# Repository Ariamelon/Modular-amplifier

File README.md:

# Modular amplifier
A PCB for a compact but complete headphone amplifier package. Designed to fit in [this](https://item.taobao.com/item.htm?id=629378026025) case.

## Key Features
* Swappable amplifier and relay attenuator modules
* Large heatsink with variable position based on thermal planes of amplifier modules
* +-13.7V voltage rails for the amplifier modules
* +5V secondary rail for the microcontroller, relays and logic
* Power on/off anti-thump functionality
* DC offset and overheat protection
* Differential/SE mode
* Mute mode
* Standby mode

An on-board ATtiny2313A-P is used to control these functions:
* 4-channel 256-step relay-based attenuator controlled via a standard pot
* RGB state indicator LED (because why not)

[PCB_Backplane](Images/Backplane-Assembly.pdf)

[PCB_Attenuator](Images/Attenuator-Assembly.pdf) 

[PCB_Omicron_Module](Images/Omicron_Module-Assembly.pdf)

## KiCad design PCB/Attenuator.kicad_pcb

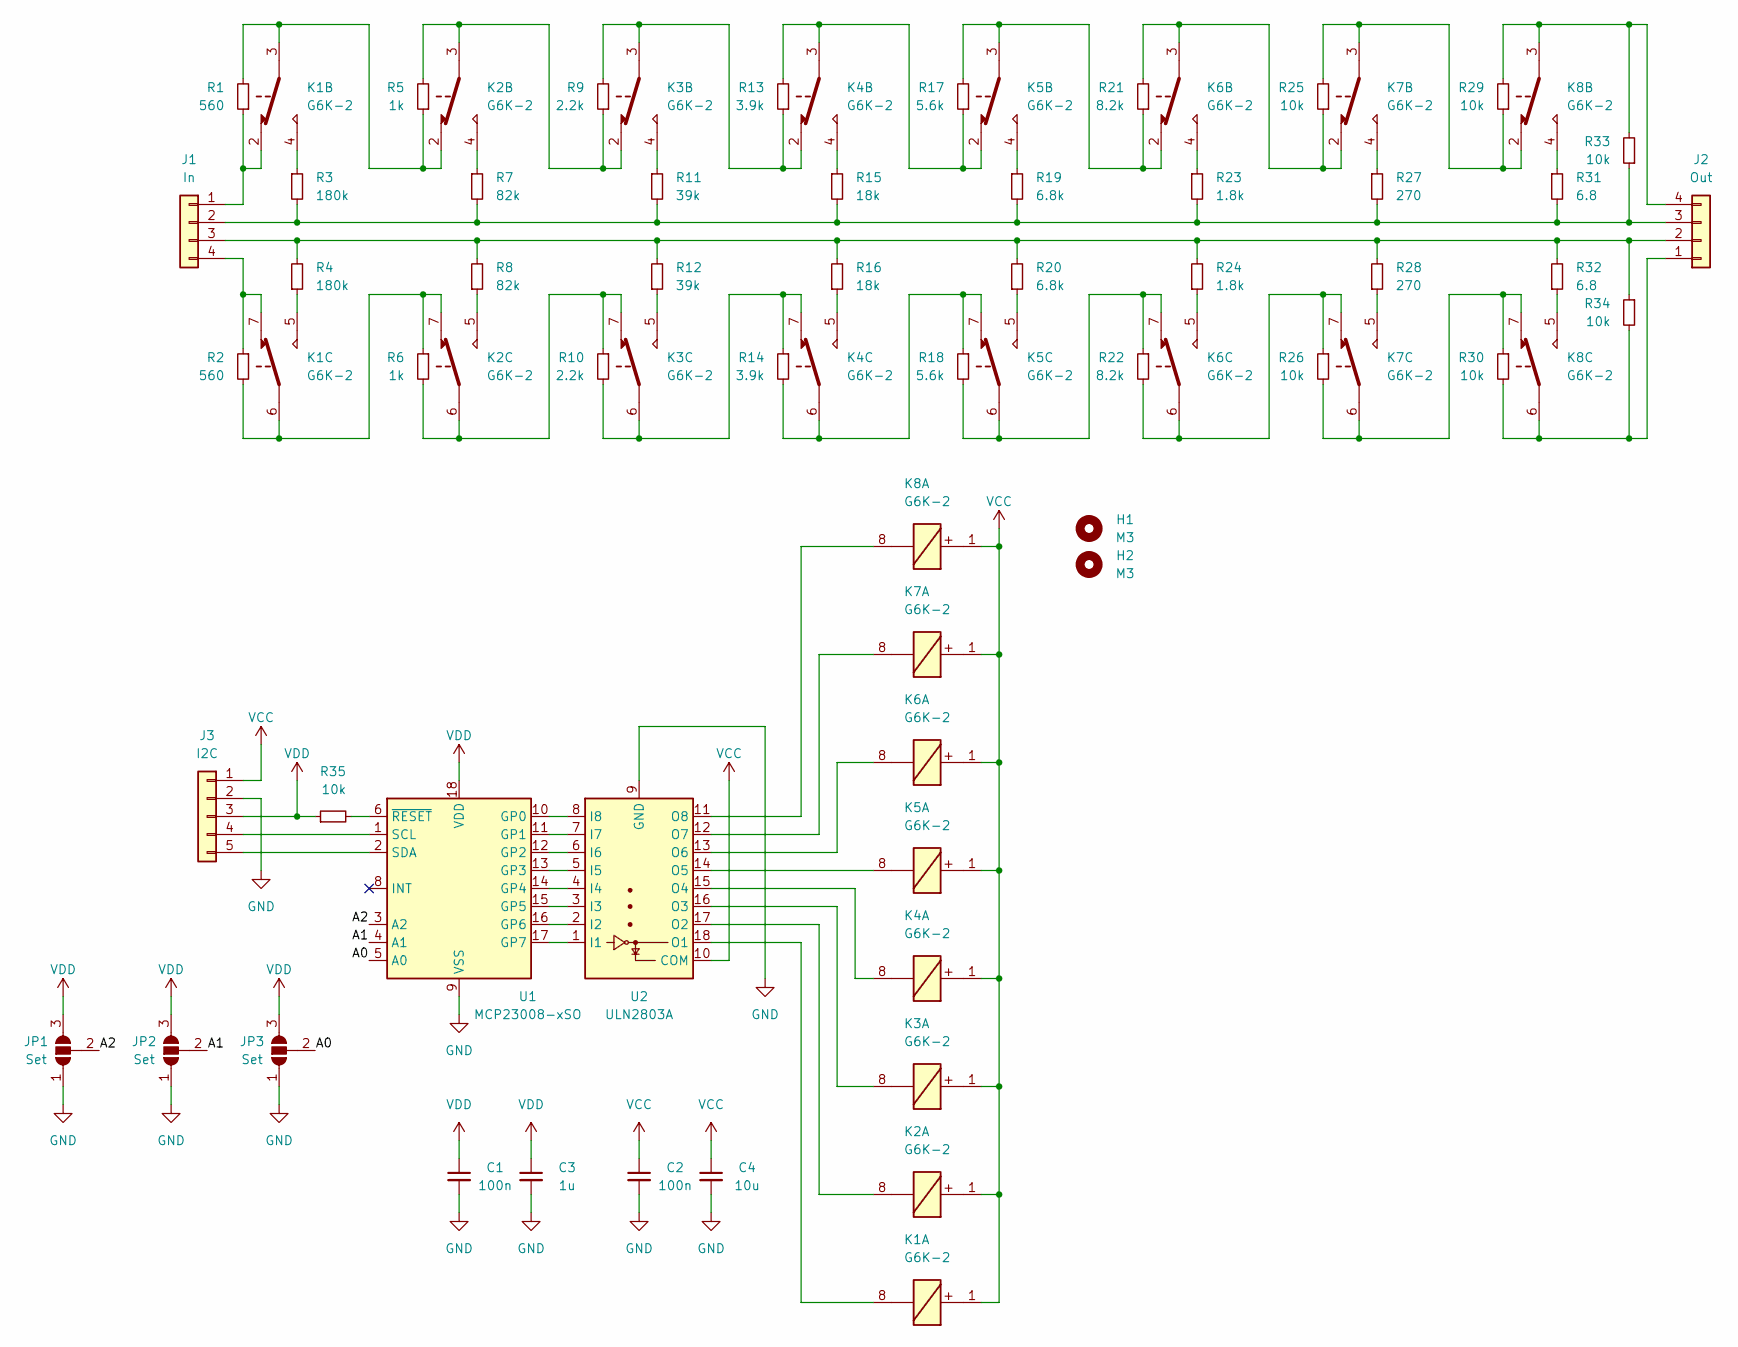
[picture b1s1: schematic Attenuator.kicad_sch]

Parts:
C1, C2: 100n; C_0603_1608Metric; Part number CL10A105KB8NNNC; LCSC part number C15849
C3: 1u; C_0603_1608Metric; Part number CL10A105KB8NNNC; LCSC part number C15849
C4: 10u; C_0603_1608Metric; Part number CL10A105KB8NNNC; LCSC part number C15849
H1, H2: M3; MountingHole_3.2mm_M3_DIN965_Pad
J1: In; PinSocket_1x04_P2.54mm_Horizontal
J2: Out; PinSocket_1x04_P2.54mm_Horizontal
J3: I2C; PinSocket_1x05_P2.54mm_Horizontal
JP1, JP2, JP3: Set; SolderJumper-3_P1.3mm_Open_RoundedPad1.0x1.5mm
K1, K2, K3, K4, K5, K6, K7, K8: G6K-2; Relay_DPDT_Omron_G6K-2P-Y
R1, R2: 560; R_1206_3216Metric
R3, R4: 180k; R_1206_3216Metric
R5, R6: 1k; R_1206_3216Metric
R7, R8: 82k; R_1206_3216Metric
R9, R10: 2.2k; R_1206_3216Metric
R11, R12: 39k; R_1206_3216Metric
R13, R14: 3.9k; R_1206_3216Metric
R15, R16: 18k; R_1206_3216Metric
R17, R18: 5.6k; R_1206_3216Metric
R19, R20: 6.8k; R_1206_3216Metric
R21, R22: 8.2k; R_1206_3216Metric
R23, R24: 1.8k; R_1206_3216Metric
R25, R26, R29, R30, R33, R34, R35: 10k; R_1206_3216Metric
R27, R28: 270; R_1206_3216Metric
R31, R32: 6.8; R_1206_3216Metric
U1: MCP23008-xSO; DIP-18_W7.62mm_Socket
U2: ULN2803A; DIP-18_W7.62mm_Socket

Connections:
/A0: JP3.2 (C), U1.5 (A0)
/A1: JP2.2 (C), U1.4 (A1)
/A2: JP1.2 (C), U1.3 (A2)
GND: C1.2, C2.2, C3.2, C4.2, J3.2, JP1.1 (A), JP2.1 (A), JP3.1 (A), U1.9 (VSS), U2.9 (GND)
unnamed: J1.1, K1.2, R1.1
unnamed: J1.2, J2.3, R3.2, R7.2, R11.2, R15.2, R19.2, R23.2, R27.2, R31.2, R33.1
unnamed: J1.3, J2.2, R4.2, R8.2, R12.2, R16.2, R20.2, R24.2, R28.2, R32.2, R34.1
unnamed: J1.4, K1.7, R2.1
unnamed: J2.1, K8.6, R30.2, R34.2
unnamed: J2.4, K8.3, R29.2, R33.2
unnamed: J3.4, U1.1 (SCL)
unnamed: J3.5, U1.2 (SDA)
unnamed: K1.3, K2.2, R1.2, R5.1
unnamed: K1.4, R3.1
unnamed: K1.5, R4.1
unnamed: K1.6, K2.7, R2.2, R6.1
unnamed: K1.8, U2.18 (O1)
unnamed: K2.3, K3.2, R5.2, R9.1
unnamed: K2.4, R7.1
unnamed: K2.5, R8.1
unnamed: K2.6, K3.7, R6.2, R10.1
unnamed: K2.8, U2.17 (O2)
unnamed: K3.3, K4.2, R9.2, R13.1
unnamed: K3.4, R11.1
unnamed: K3.5, R12.1
unnamed: K3.6, K4.7, R10.2, R14.1
unnamed: K3.8, U2.16 (O3)
unnamed: K4.3, K5.2, R13.2, R17.1
unnamed: K4.4, R15.1
unnamed: K4.5, R16.1
unnamed: K4.6, K5.7, R14.2, R18.1
unnamed: K4.8, U2.15 (O4)
unnamed: K5.3, K6.2, R17.2, R21.1
unnamed: K5.4, R19.1
unnamed: K5.5, R20.1
unnamed: K5.6, K6.7, R18.2, R22.1
unnamed: K5.8, U2.14 (O5)
unnamed: K6.3, K7.2, R21.2, R25.1
unnamed: K6.4, R23.1
unnamed: K6.5, R24.1
unnamed: K6.6, K7.7, R22.2, R26.1
unnamed: K6.8, U2.13 (O6)
unnamed: K7.3, K8.2, R25.2, R29.1
unnamed: K7.4, R27.1
unnamed: K7.5, R28.1
unnamed: K7.6, K8.7, R26.2, R30.1
unnamed: K7.8, U2.12 (O7)
unnamed: K8.4, R31.1
unnamed: K8.5, R32.1
unnamed: K8.8, U2.11 (O8)
unnamed: R35.2, U1.6 (~RESET)
unnamed: U1.10 (GP0), U2.8 (I8)
unnamed: U1.11 (GP1), U2.7 (I7)
unnamed: U1.12 (GP2), U2.6 (I6)
unnamed: U1.13 (GP3), U2.5 (I5)
unnamed: U1.14 (GP4), U2.4 (I4)
unnamed: U1.15 (GP5), U2.3 (I3)
unnamed: U1.16 (GP6), U2.2 (I2)
unnamed: U1.17 (GP7), U2.1 (I1)
VCC: C2.1, C4.1, J3.1, K1.1, K2.1, K3.1, K4.1, K5.1, K6.1, K7.1, K8.1, U2.10 (COM)
VDD: C1.1, C3.1, J3.3, JP1.3 (B), JP2.3 (B), JP3.3 (B), R35.1, U1.18 (VDD)

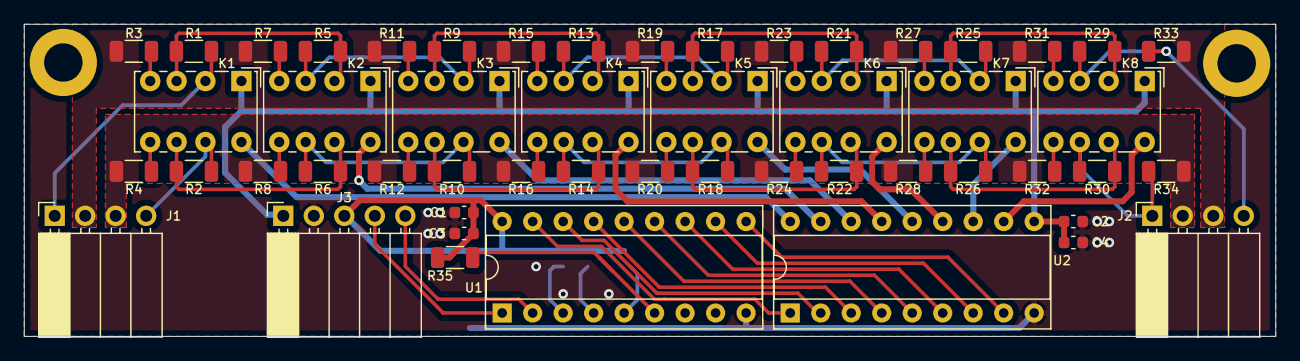
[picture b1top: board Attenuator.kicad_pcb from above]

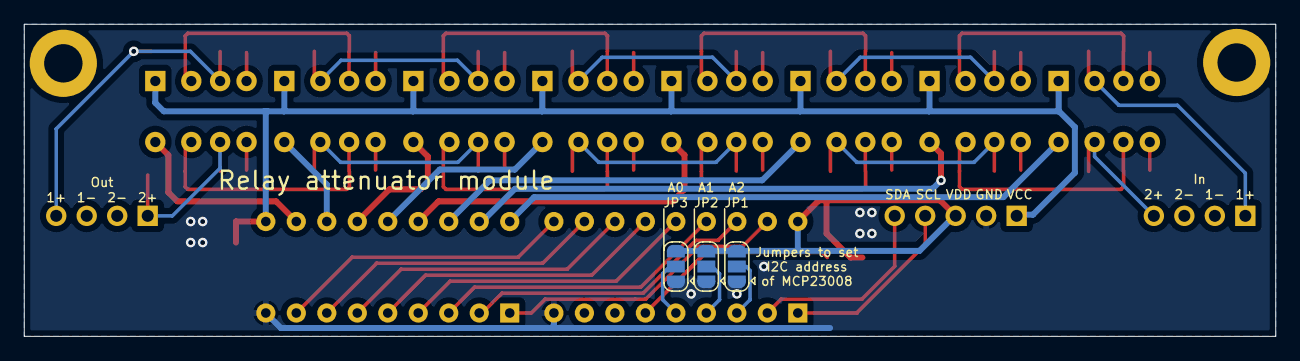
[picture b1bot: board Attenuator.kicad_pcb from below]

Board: 2 copper layers, 104.2 x 26.0 mm, 57 parts (3 on the bottom side), 61 nets.

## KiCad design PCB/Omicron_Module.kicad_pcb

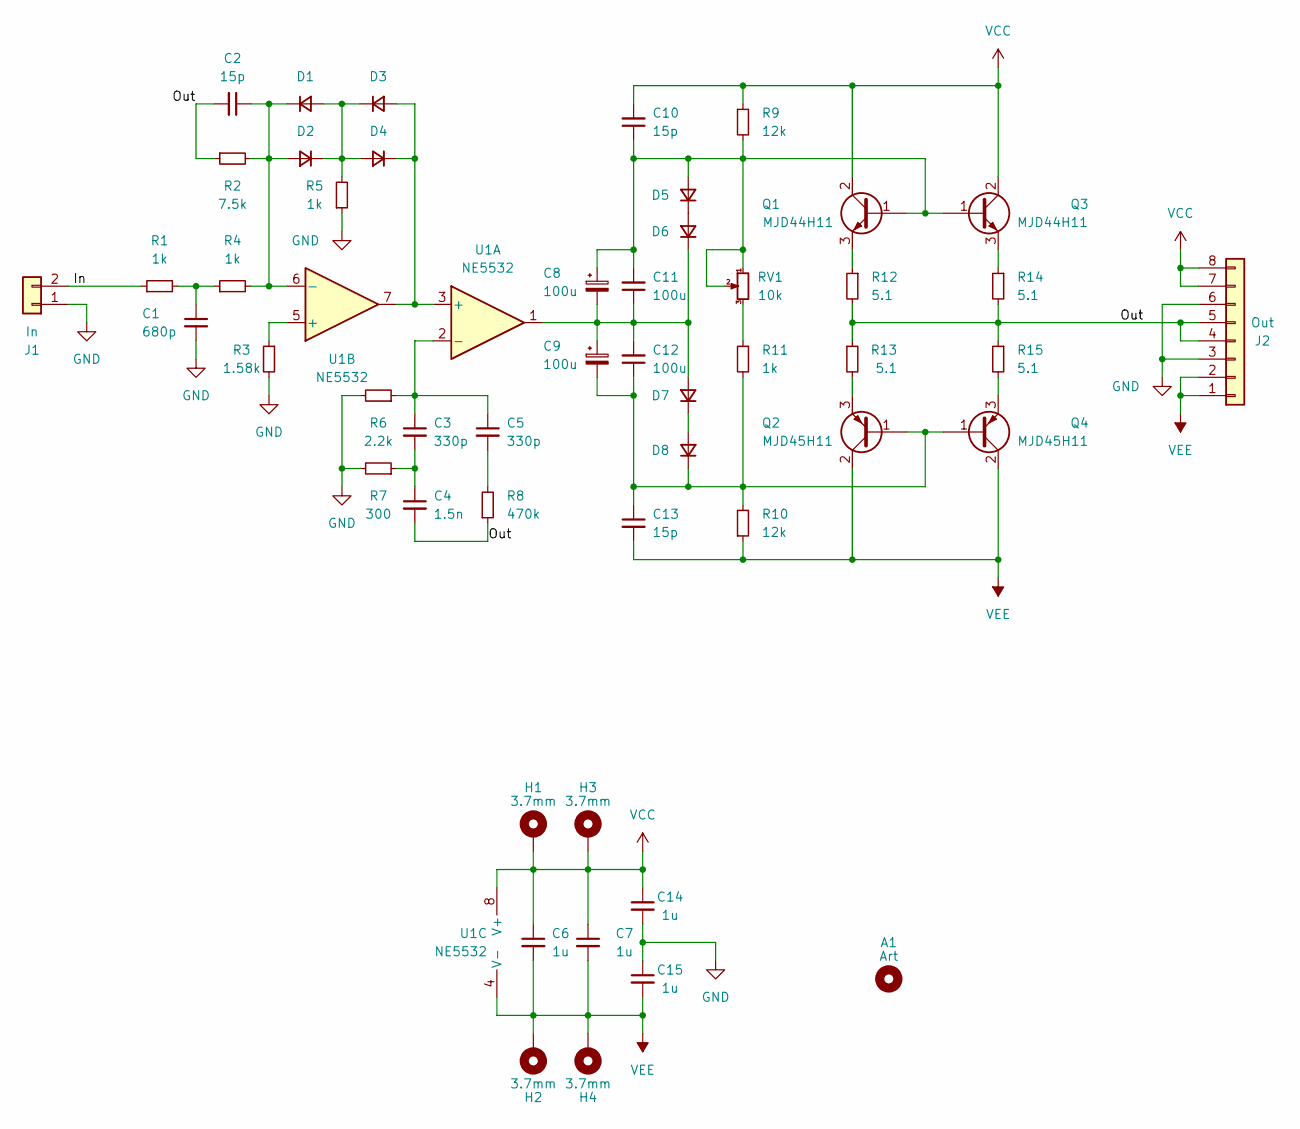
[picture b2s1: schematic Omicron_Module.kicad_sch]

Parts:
A1: Art; Ariamelon_Logo_CU
C1: 680p; C_0603_1608Metric
C2, C10, C13: 15p; C_0603_1608Metric
C3, C5: 330p; C_0603_1608Metric
C4: 1.5n; C_0603_1608Metric
C6, C7, C14, C15: 1u; C_0603_1608Metric; Part number CL10A105KB8NNNC; LCSC part number C15849
C8, C9: 100u; CP_Elec_8x6.9; Part number EEE-FK1V101GV
C11, C12: 100u; C_Radial_D8.0mm_H11.5mm_P3.50mm_Sideways; Part number EEE-FK1V101GV
D1, D2, D3, D4, D5, D6, D7, D8: D; D_SOD-123; Part number 1N4148W; LCSC part number C81598
H1, H2, H3, H4: 3.7mm; MountingHole_3.2mm_M3_DIN965_Pad_3.7mm_Hole
J1: In; PinHeader_1x02_P2.54mm_Vertical
J2: Out; PinHeader_1x08_P2.54mm_Vertical
Q1, Q3: MJD44H11; TO-252-2
Q2, Q4: MJD45H11; TO-252-2
R1, R4, R5, R11: 1k; R_1206_3216Metric
R2: 7.5k; R_1206_3216Metric
R3: 1.58k; R_1206_3216Metric
R6: 2.2k; R_1206_3216Metric
R7: 300; R_1206_3216Metric
R8: 470k; R_1206_3216Metric
R9, R10: 12k; R_1206_3216Metric
R12, R13, R14, R15: 5.1; R_1206_3216Metric
RV1: 10k; Potentiometer_Bourns_TC33X_Vertical
U1: NE5532; SOIC-8_3.9x4.9mm_P1.27mm

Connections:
/In: J1.2, R1.1
/Out: C2.2, C4.2, J2.4, J2.5, R2.1, R8.1, R12.2, R13.1, R14.2, R15.1
GND: C1.2, C14.2, C15.1, J1.1, J2.3, J2.6, R3.2, R5.1, R6.2, R7.2
unnamed: C1.1, R1.2, R4.1
unnamed: C2.1, D1.1 (K), D2.2 (A), R2.2, R4.2, U1.6 (-)
unnamed: C3.1, C5.1, R6.1, U1.2 (-)
unnamed: C3.2, C4.1, R7.1
unnamed: C5.2, R8.2
unnamed: C8.1, C10.1, C11.2, D5.2 (A), Q1.1 (B), Q3.1 (B), R9.2, RV1.1, RV1.2
unnamed: C8.2, C9.1, C11.1, C12.2, D6.1 (K), D7.2 (A), U1.1
unnamed: C9.2, C12.1, C13.1, D8.1 (K), Q2.1 (B), Q4.1 (B), R10.2, R11.2
unnamed: D1.2 (A), D2.1 (K), D3.1 (K), D4.2 (A), R5.2
unnamed: D3.2 (A), D4.1 (K), U1.3 (+), U1.7
unnamed: D5.1 (K), D6.2 (A)
unnamed: D7.1 (K), D8.2 (A)
unnamed: Q1.3 (E), R12.1
unnamed: Q2.3 (E), R13.2
unnamed: Q3.3 (E), R14.1
unnamed: Q4.3 (E), R15.2
unnamed: R3.1, U1.5 (+)
unnamed: R11.1, RV1.3
VCC: C6.1, C7.1, C10.2, C14.1, H1.1, H3.1, J2.7, J2.8, Q1.2 (C), Q3.2 (C), R9.1, U1.8 (V+)
VEE: C6.2, C7.2, C13.2, C15.2, H2.1, H4.1, J2.1, J2.2, Q2.2 (C), Q4.2 (C), R10.1, U1.4 (V-)

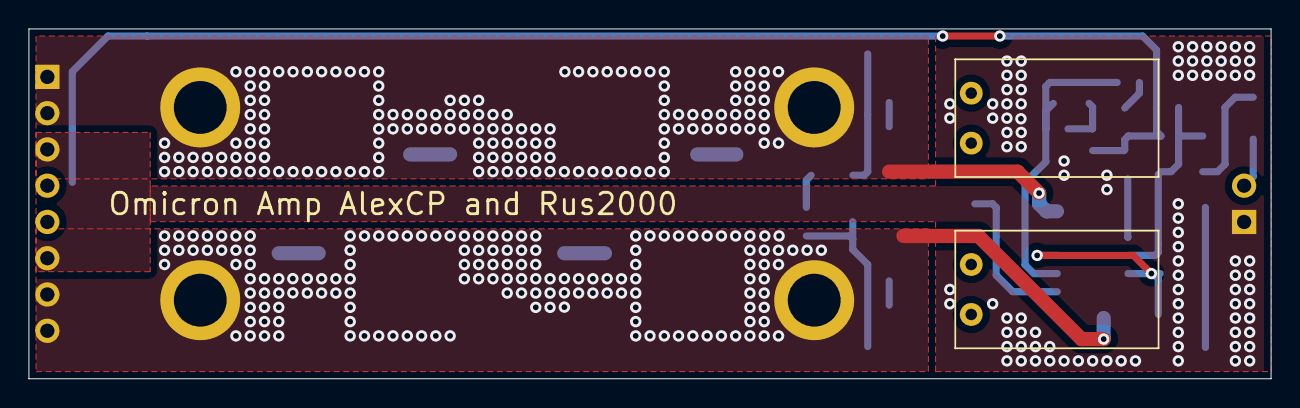
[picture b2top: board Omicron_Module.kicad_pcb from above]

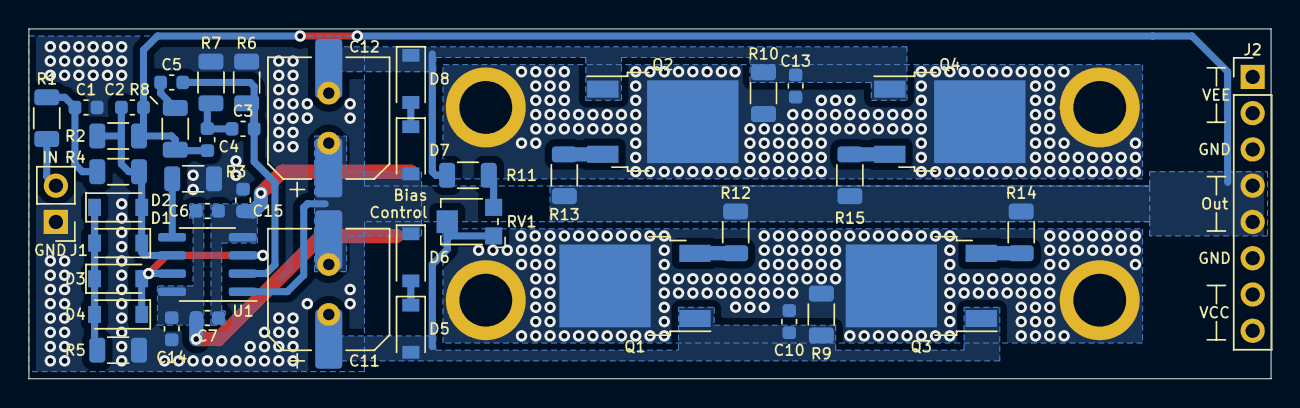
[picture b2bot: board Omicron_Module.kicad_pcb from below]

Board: 2 copper layers, 87.0 x 24.5 mm, 51 parts (48 on the bottom side), 23 nets.

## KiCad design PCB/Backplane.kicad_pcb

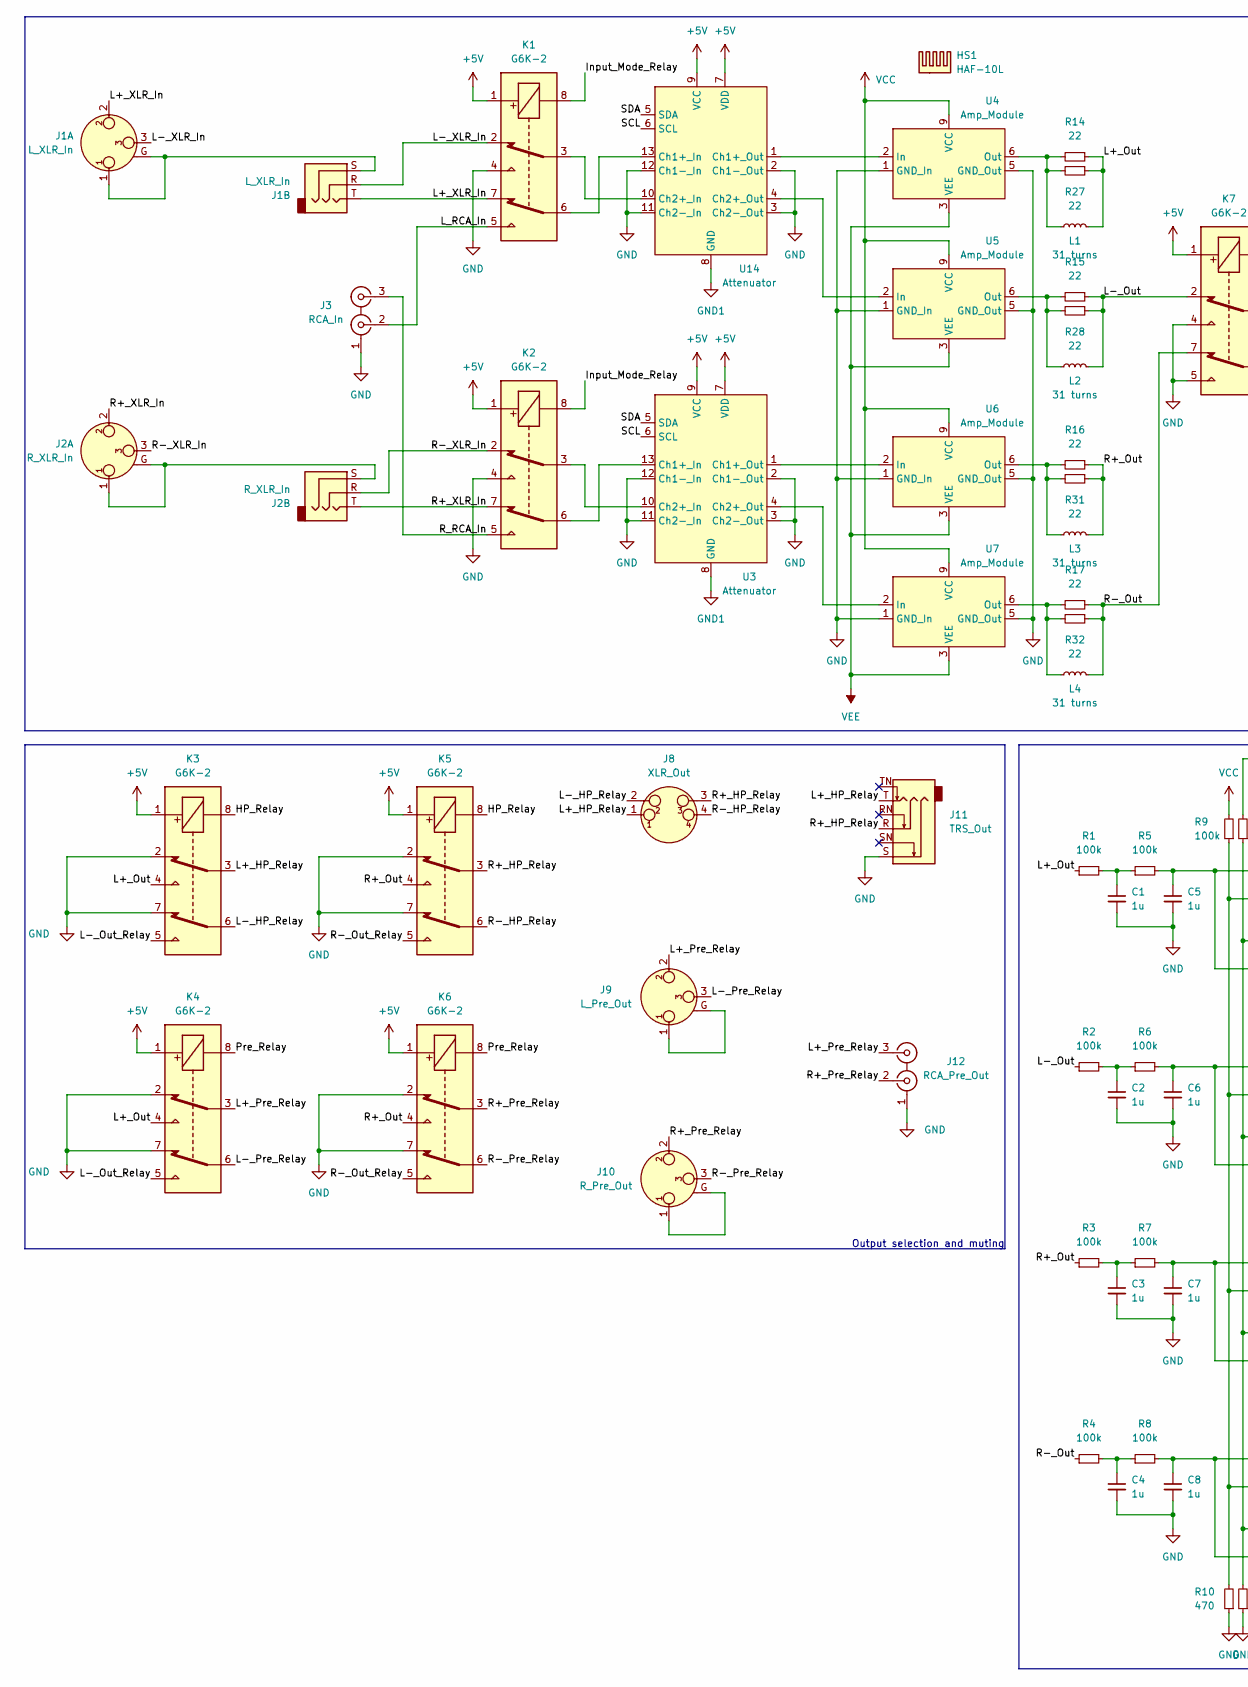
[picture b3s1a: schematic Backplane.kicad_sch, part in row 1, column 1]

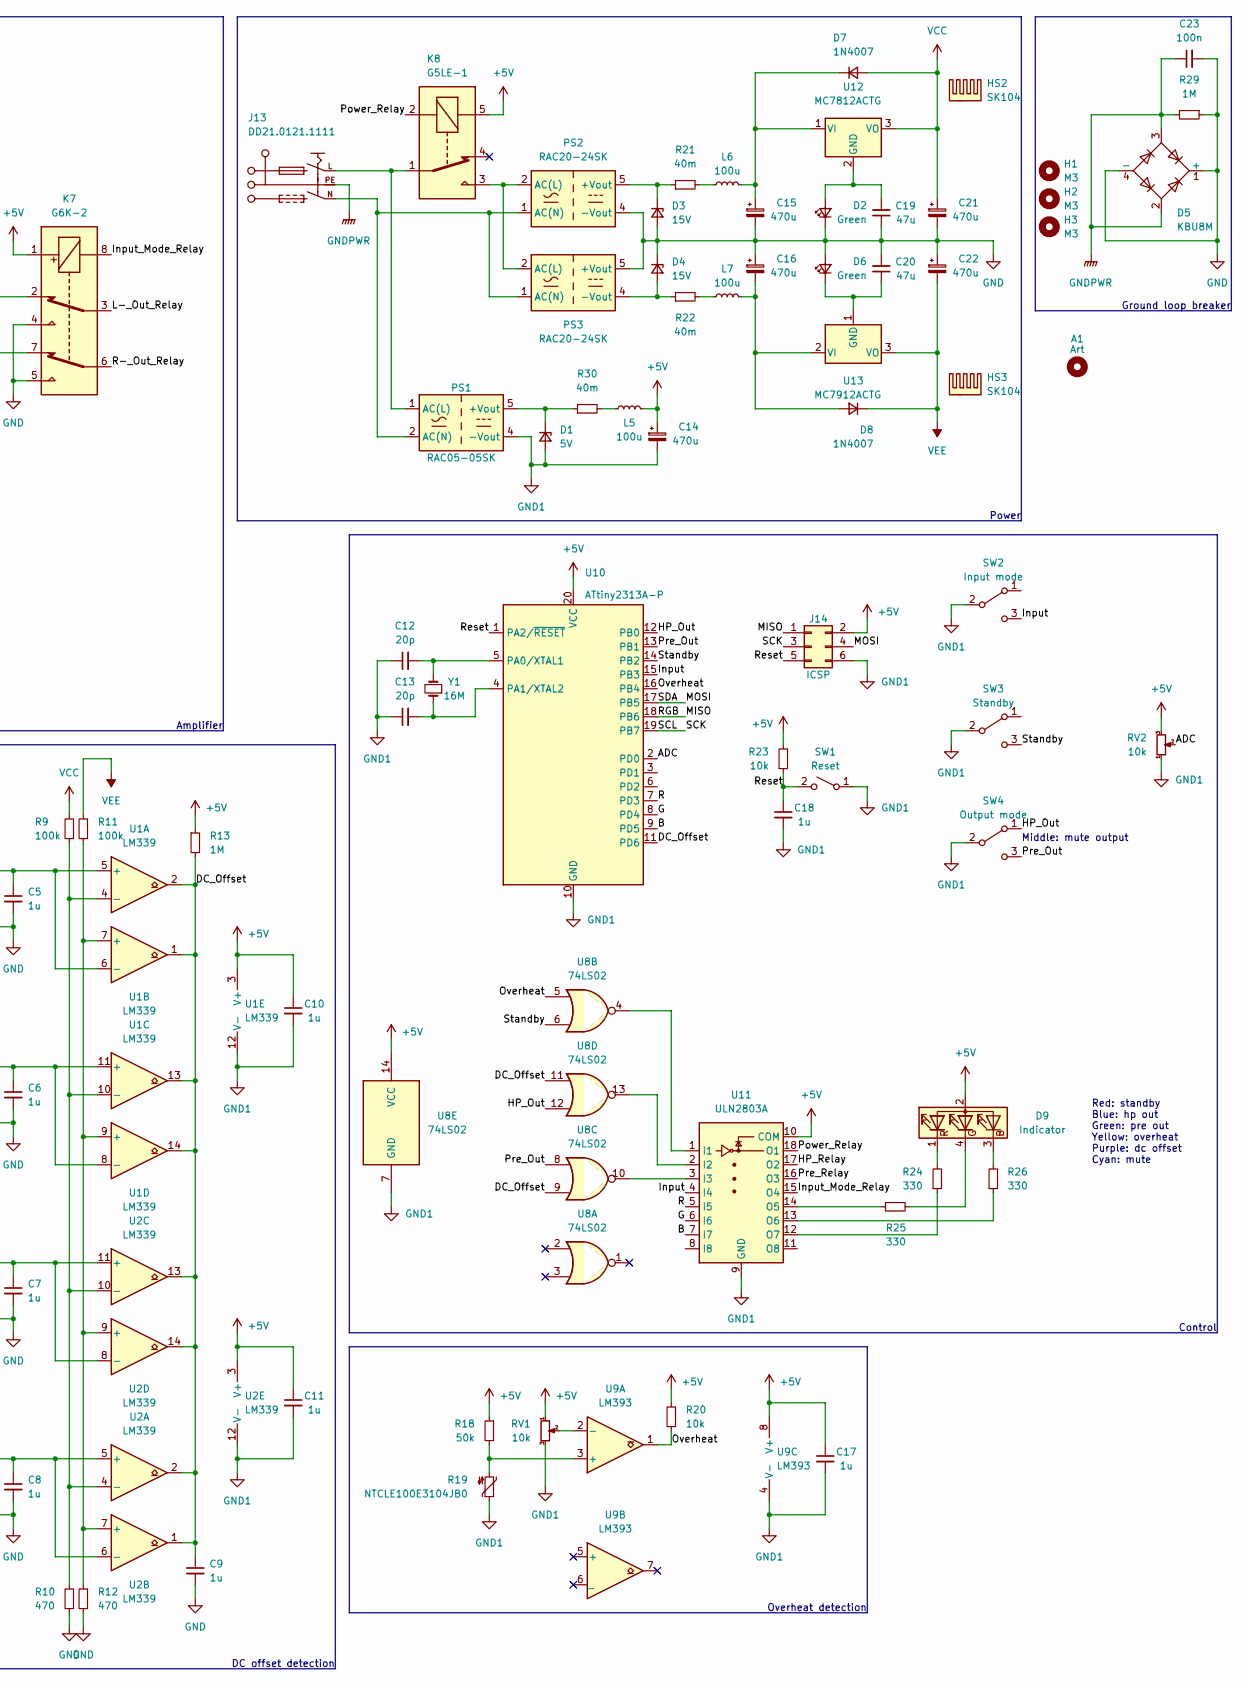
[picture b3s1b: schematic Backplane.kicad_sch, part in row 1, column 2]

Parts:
A1: Art; Ariamelon_Logo_x3_CU
C1, C2, C3, C4, C5, C6, C7, C8: 1u; C_0603_1608Metric
C9, C10, C11, C17, C18: 1u; C_0603_1608Metric; Part number CL10A105KB8NNNC; LCSC part number C15849
C12, C13: 20p; C_0603_1608Metric
C14, C15, C16, C21, C22: 470u; CP_Elec_8x10.5; Part number EEEFT1E471GP; LCSC part number C193277
C19, C20: 47u; C_1206_3216Metric
C23: 100n; C_Rect_L26.5mm_W8.5mm_P22.50mm_MKS4; Part number PHE820ED6100MR06L2; LCSC part number C2926846
D1: 5V; D_SOD-123; LCSC part number C193402
D2, D6: Green; LED_D5.0mm
D3, D4: 15V; D_SMC; Part number SMCJ15CA-13-F
D5: KBU8M; Diode_Bridge_Vishay_KBU
D7, D8: 1N4007; D_SMA
D9: Indicator; LED_D5.0mm-4_RGB_Staggered_Pins
H1, H2, H3: M3; MountingHole_3.2mm_M3
HS1: HAF-10L
HS2, HS3: SK104; Heatsink_Fischer_SK104-STC-STIC_35x13mm_2xDrill2.5mm
J1: L_XLR_In; Jack_XLR-6.35mm_Neutrik_NCJ6FA-H_Horizontal
J2: R_XLR_In; Jack_XLR-6.35mm_Neutrik_NCJ6FA-H_Horizontal
J3: RCA_In; RCJ-2221
J8: XLR_Out; Jack_XLR_Neutrik_NC4FAH_Horizontal
J9: L_Pre_Out; Jack_XLR_Neutrik_NC3MAH_Horizontal
J10: R_Pre_Out; Jack_XLR_Neutrik_NC3MAH_Horizontal
J11: TRS_Out; Jack_6.35mm_Neutrik_NMJ6HCD2_Horizontal
J12: RCA_Pre_Out; RCJ-2221
J13: DD21.0121.1111; SCHURTER_DD21.0121.1111
J14: ICSP; PinHeader_2x03_P2.54mm_Vertical
K1, K2, K3, K4, K5, K6, K7: G6K-2; Relay_DPDT_Omron_G6K-2P-Y
K8: G5LE-1; Relay_SPDT_Omron-G5LE-1
L1, L2, L3, L4: 31 turns; L_Toroid_D15mm_W4mm; Part number N/A; LCSC part number N/A
L5, L6, L7: 100u; L_TDK_SLF7032; Part number SPM7054VT-101M-D; LCSC part number C2045491
PS1: RAC05-05SK; Converter_ACDC_RECOM_RAC05-xxSK_THT
PS2, PS3: RAC20-24SK; Converter_ACDC_Recom_RAC20-xxSK_THT
R1, R2, R3, R4, R5, R6, R7, R8, R9, R11: 100k; R_1206_3216Metric; Part number RT1206FRD0710KL; LCSC part number C705072
R10, R12: 470; R_1206_3216Metric; Part number RT1206FRD0710KL; LCSC part number C705072
R13: 1M; R_1206_3216Metric; Part number RT1206FRE071ML; LCSC part number C375528
R14, R15, R16, R17, R27, R28, R31, R32: 22; R_1206_3216Metric; Part number RT1206FRD073RL; LCSC part number C326707
R18: 50k; R_1206_3216Metric; Part number RT1206FRD0710KL; LCSC part number C705072
R19: NTCLE100E3104JB0; C_Disc_D3.4mm_W2.1mm_P2.50mm
R20, R23: 10k; R_1206_3216Metric; Part number RT1206FRD0710KL; LCSC part number C705072
R21, R22, R30: 40m; OAR1; Part number RT1206BRD074R99L; LCSC part number C326584
R24, R25, R26: 330; R_1206_3216Metric; Part number RT1206FRD0710KL; LCSC part number C705072
R29: 1M; R_Radial_Power_L13.0mm_W9.0mm_P5.00mm; Part number RT1206FRE071ML; LCSC part number C375528
RV1: 10k; Potentiometer_Bourns_3266W_Vertical
RV2: 10k; Potentiometer_Alps_RK163_Single_Horizontal
SW1: Reset; SW_PUSH_6mm
SW2: Input mode; 100SP1T2B4M7RE; Part number 100SP1T2B4M7RE
SW3: Standby; 100SP1T2B4M7RE; Part number 100SP1T2B4M7RE
SW4: Output mode; 100SP1T2B4M7RE; Part number 100SP1T2B4M7RE
U1, U2: LM339; DIP-14_W7.62mm_Socket
U3, U14: Attenuator
U4, U5, U6, U7: Amp_Module
U8: 74LS02; DIP-14_W7.62mm_Socket
U9: LM393; DIP-8_W7.62mm_Socket
U10: ATtiny2313A-P; DIP-20_W7.62mm_Socket
U11: ULN2803A; DIP-18_W7.62mm_Socket
U12: MC7812ACTG; TO-220-3_Vertical
U13: MC7912ACTG; TO-220-3_Vertical
Y1: 16M; Crystal_HC52-6mm_Vertical

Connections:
+5V: C10.1, C11.1, C14.1, C17.1, D9.2 (A), J14.2, K1.1, K2.1, K3.1, K4.1, K5.1, K6.1, K7.1, K8.5, L5.2, R13.1, R18.1, R20.2, R23.2, RV1.1, RV2.3, U1.3 (V+), U2.3 (V+), U3.7 (VDD), U3.9 (VCC), U8.14 (VCC), U9.8 (V+), U10.20 (VCC), U11.10 (COM), U14.7 (VDD), U14.9 (VCC)
/ADC: RV2.2, U10.2 (PD0)
/B: U10.9 (PD5), U11.7 (I7)
/DC_Offset: C9.1, R13.2, U1.1, U1.2, U1.13, U1.14, U2.1, U2.2, U2.13, U2.14, U8.9, U8.11, U10.11 (PD6)
/G: U10.8 (PD4), U11.6 (I6)
/HP_Out: SW4.1 (A), U8.12, U10.12 (PB0)
/HP_Relay: K3.8, K5.8, U11.17 (O2)
/Input: SW2.3 (C), U10.15 (PB3), U11.4 (I4)
/Input_Mode_Relay: K1.8, K2.8, K7.8, U11.15 (O4)
/L+_HP_Relay: J8.1, J11.T, K3.3
/L+_Out: K3.4, K4.4, L1.2, R1.1, R14.1, R27.1
/L+_Pre_Relay: J9.2, J12.3 (IN1), K4.3
/L+_XLR_In: J1.2, J1.T, K1.7
/L-_HP_Relay: J8.2, K3.6
/L-_Out: K7.2, L2.2, R2.1, R15.1, R28.1
/L-_Out_Relay: K3.5, K4.5, K7.3
/L-_Pre_Relay: J9.3, K4.6
/L-_XLR_In: J1.3, J1.R, K1.2
/L_RCA_In: J3.2 (IN2), K1.5
/MISO: J14.1, U10.18 (PB6)
/MOSI: J14.4, U3.5 (SDA), U10.17 (PB5), U14.5 (SDA)
/Overheat: R20.1, U8.5, U9.1, U10.16 (PB4)
/Power_Relay: K8.2, U11.18 (O1)
/Pre_Out: SW4.3 (C), U8.8, U10.13 (PB1)
/Pre_Relay: K4.8, K6.8, U11.16 (O3)
/R: U10.7 (PD3), U11.5 (I5)
/R+_HP_Relay: J8.3, J11.R, K5.3
/R+_Out: K5.4, K6.4, L3.2, R3.1, R16.1, R31.1
/R+_Pre_Relay: J10.2, J12.2 (IN2), K6.3
/R+_XLR_In: J2.2, J2.T, K2.7
/R-_HP_Relay: J8.4, K5.6
/R-_Out: K7.7, L4.2, R4.1, R17.1, R32.1
/R-_Out_Relay: K5.5, K6.5, K7.6
/R-_Pre_Relay: J10.3, K6.6
/R-_XLR_In: J2.3, J2.R, K2.2
/R_RCA_In: J3.3 (IN1), K2.5
/Reset: C18.1, J14.5, R23.1, SW1.2 (B), U10.1 (PA2/~RESET)
/SCK: J14.3, U3.6 (SCL), U10.19 (PB7), U14.6 (SCL)
/Standby: SW3.3 (C), U8.6, U10.14 (PB2)
GND: C1.2, C2.2, C3.2, C4.2, C5.2, C6.2, C7.2, C8.2, C9.2, C15.2, C16.1, C19.1, C20.2, C21.2, C22.1, C23.2, D2.1 (K), D3.2 (A), D4.1 (K), D5.1 (+), D5.4 (-), D6.2 (A), J3.1 (EXT), J11.S, J12.1 (EXT), K1.4, K2.4, K3.2, K3.7, K4.2, K4.7, K5.2, K5.7, K6.2, K6.7, K7.4, K7.5, PS2.4 (-Vout), PS3.5 (+Vout), R10.1, R12.1, R29.1, U3.2 (Ch1-_Out), U3.3 (Ch2-_Out), U3.11 (Ch2-_In), U3.12 (Ch1-_In), U4.1 (GND_In), U4.5 (GND_Out), U4.8 (GND_Out), U5.1 (GND_In), U5.5 (GND_Out), U5.8 (GND_Out), U6.1 (GND_In), U6.5 (GND_Out), U6.8 (GND_Out), U7.1 (GND_In), U7.5 (GND_Out), U7.8 (GND_Out), U14.2 (Ch1-_Out), U14.3 (Ch2-_Out), U14.11 (Ch2-_In), U14.12 (Ch1-_In)
GND1: C10.2, C11.2, C12.1, C13.1, C14.2, C17.2, C18.2, D1.2 (A), J14.6, PS1.4 (-Vout), R19.1, RV1.3, RV2.1, SW1.1 (A), SW2.2 (B), SW3.2 (B), SW4.2 (B), U1.12 (V-), U2.12 (V-), U3.8 (GND), U8.7 (GND), U9.4 (V-), U10.10 (GND), U11.9 (GND), U14.8 (GND)
GNDPWR: C23.1, D5.2, D5.3, J13.PE, R29.2
unnamed: C1.1, R1.2, R5.1
unnamed: C2.1, R2.2, R6.1
unnamed: C3.1, R3.2, R7.1
unnamed: C4.1, R4.2, R8.1
unnamed: C5.1, R5.2, U1.5 (+), U1.6 (-)
unnamed: C6.1, R6.2, U1.8 (-), U1.11 (+)
unnamed: C7.1, R7.2, U2.8 (-), U2.11 (+)
unnamed: C8.1, R8.2, U2.5 (+), U2.6 (-)
unnamed: C12.2, U10.5 (PA0/XTAL1), Y1.2
unnamed: C13.2, U10.4 (PA1/XTAL2), Y1.1
unnamed: C15.1, D7.1 (K), L6.2, U12.1 (VI)
unnamed: C16.2, D8.2 (A), L7.2, U13.2 (VI)
unnamed: C19.2, D2.2 (A), U12.2 (GND)
unnamed: C20.1, D6.1 (K), U13.1 (GND)
unnamed: D1.1 (K), PS1.5 (+Vout), R30.1
unnamed: D3.1 (K), PS2.5 (+Vout), R21.1
unnamed: D4.2 (A), PS3.4 (-Vout), R22.1
unnamed: D9.1 (RK), R24.2
unnamed: D9.3 (BK), R26.2
unnamed: D9.4 (GK), R25.2
unnamed: J1.1, J1.G, J1.S
unnamed: J2.1, J2.G, J2.S
unnamed: J9.1, J9.G
unnamed: J10.1, J10.G
unnamed: J13.L, K8.1, PS1.1 (AC(L))
unnamed: J13.N, PS1.2 (AC(N)), PS2.1 (AC(N)), PS3.1 (AC(N))
unnamed: K1.3, U14.10 (Ch2+_In)
unnamed: K1.6, U14.13 (Ch1+_In)
unnamed: K2.3, U3.10 (Ch2+_In)
unnamed: K2.6, U3.13 (Ch1+_In)
unnamed: K8.3, PS2.2 (AC(L)), PS3.2 (AC(L))
unnamed: L1.1, R14.2, R27.2, U4.6 (Out), U4.7 (Out)
unnamed: L2.1, R15.2, R28.2, U5.6 (Out), U5.7 (Out)
unnamed: L3.1, R16.2, R31.2, U6.6 (Out), U6.7 (Out)
unnamed: L4.1, R17.2, R32.2, U7.6 (Out), U7.7 (Out)
unnamed: L5.1, R30.2
unnamed: L6.1, R21.2
unnamed: L7.1, R22.2
unnamed: R9.1, R10.2, U1.4 (-), U1.10 (-), U2.4 (-), U2.10 (-)
unnamed: R11.1, R12.2, U1.7 (+), U1.9 (+), U2.7 (+), U2.9 (+)
unnamed: R18.2, R19.2, U9.3 (+)
unnamed: R24.1, U11.12 (O7)
unnamed: R25.1, U11.14 (O5)
unnamed: R26.1, U11.13 (O6)
unnamed: RV1.2, U9.2 (-)
unnamed: U3.1 (Ch1+_Out), U6.2 (In)
unnamed: U3.4 (Ch2+_Out), U7.2 (In)
unnamed: U8.4, U11.1 (I1)
unnamed: U8.13, U11.2 (I2)
unnamed: U8.10, U11.3 (I3)
unnamed: U4.2 (In), U14.1 (Ch1+_Out)
unnamed: U5.2 (In), U14.4 (Ch2+_Out)
VCC: C21.1, D7.2 (A), R9.2, U4.9 (VCC), U4.10 (VCC), U5.9 (VCC), U5.10 (VCC), U6.9 (VCC), U6.10 (VCC), U7.9 (VCC), U7.10 (VCC), U12.3 (VO)
VEE: C22.2, D8.1 (K), R11.2, U4.3 (VEE), U4.4 (VEE), U5.3 (VEE), U5.4 (VEE), U6.3 (VEE), U6.4 (VEE), U7.3 (VEE), U7.4 (VEE), U13.3 (VO)

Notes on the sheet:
Power
Red: standby Blue: hp out Green: pre out Yellow: overheat Purple: dc offset Cyan: mute
Overheat detection
Control
Amplifier
DC offset detection
Output selection and muting
Ground loop breaker
Middle: mute output

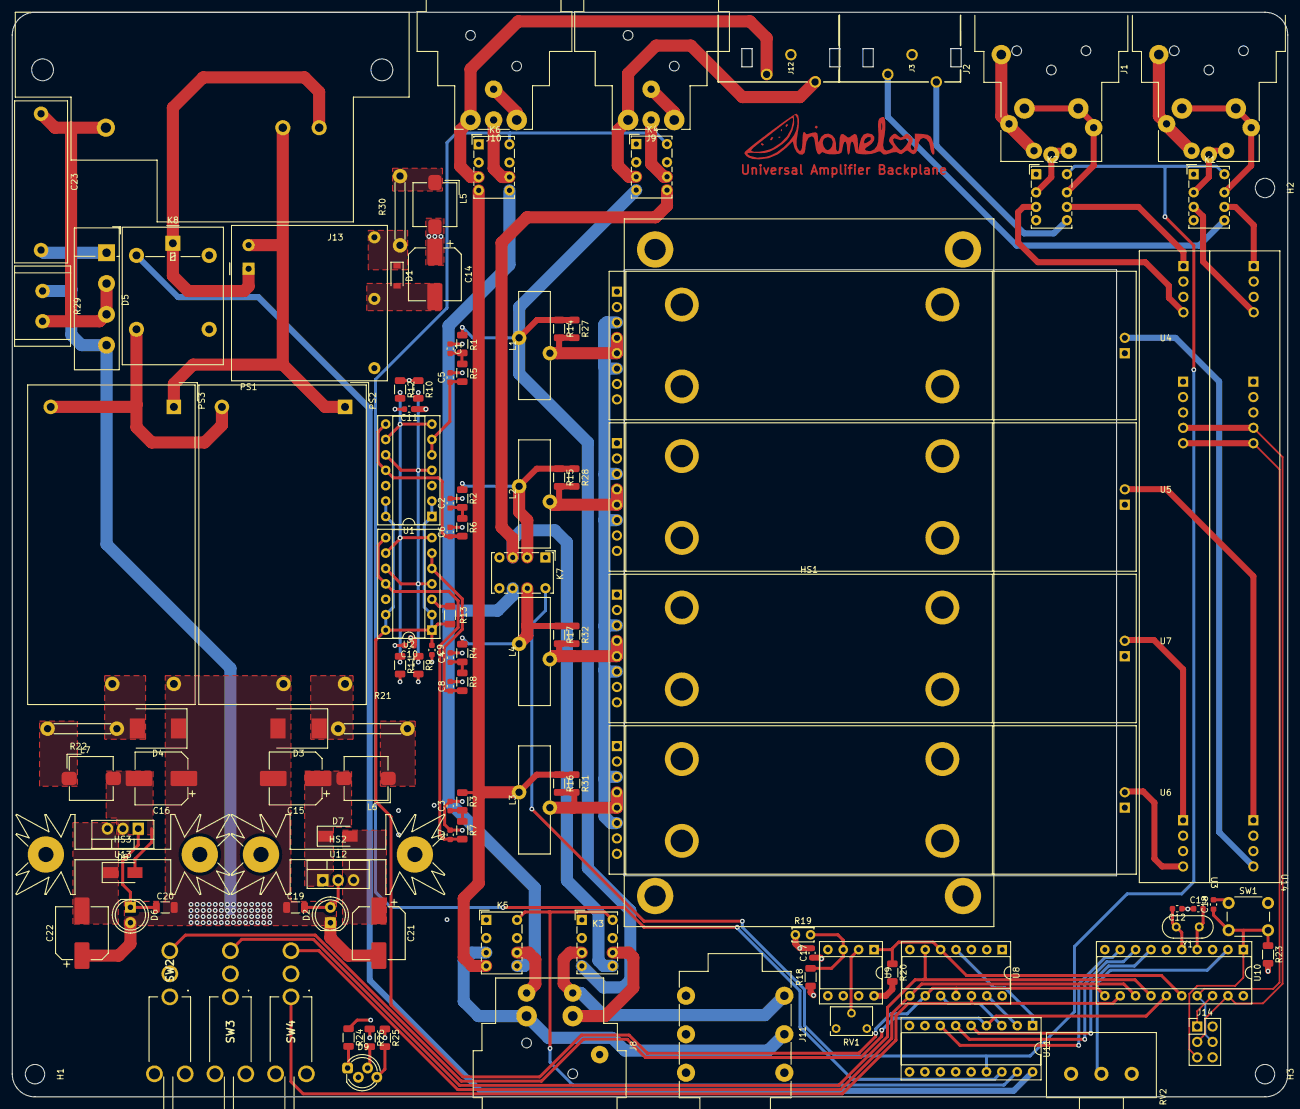
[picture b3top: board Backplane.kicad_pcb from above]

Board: 4 copper layers, 210.5 x 179.0 mm, 120 parts (0 on the bottom side), 96 nets.

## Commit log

2022-06-30 Updated resistor values
2022-06-30 Added images, fixed gerbers, fixed attenuator silk
2022-06-30 Updated silk, created heatsink rails to allow moving of heatsink position
2022-06-30 Updated images
2022-07-01 Uploaded more legible PDF files of the copper layers
2022-07-01 Added 1u decoupling capacitors to ICs on backplane and attenuator boards
2022-07-01 Added bulk capacitance to each IC, rerouted 5V line on backplane board
